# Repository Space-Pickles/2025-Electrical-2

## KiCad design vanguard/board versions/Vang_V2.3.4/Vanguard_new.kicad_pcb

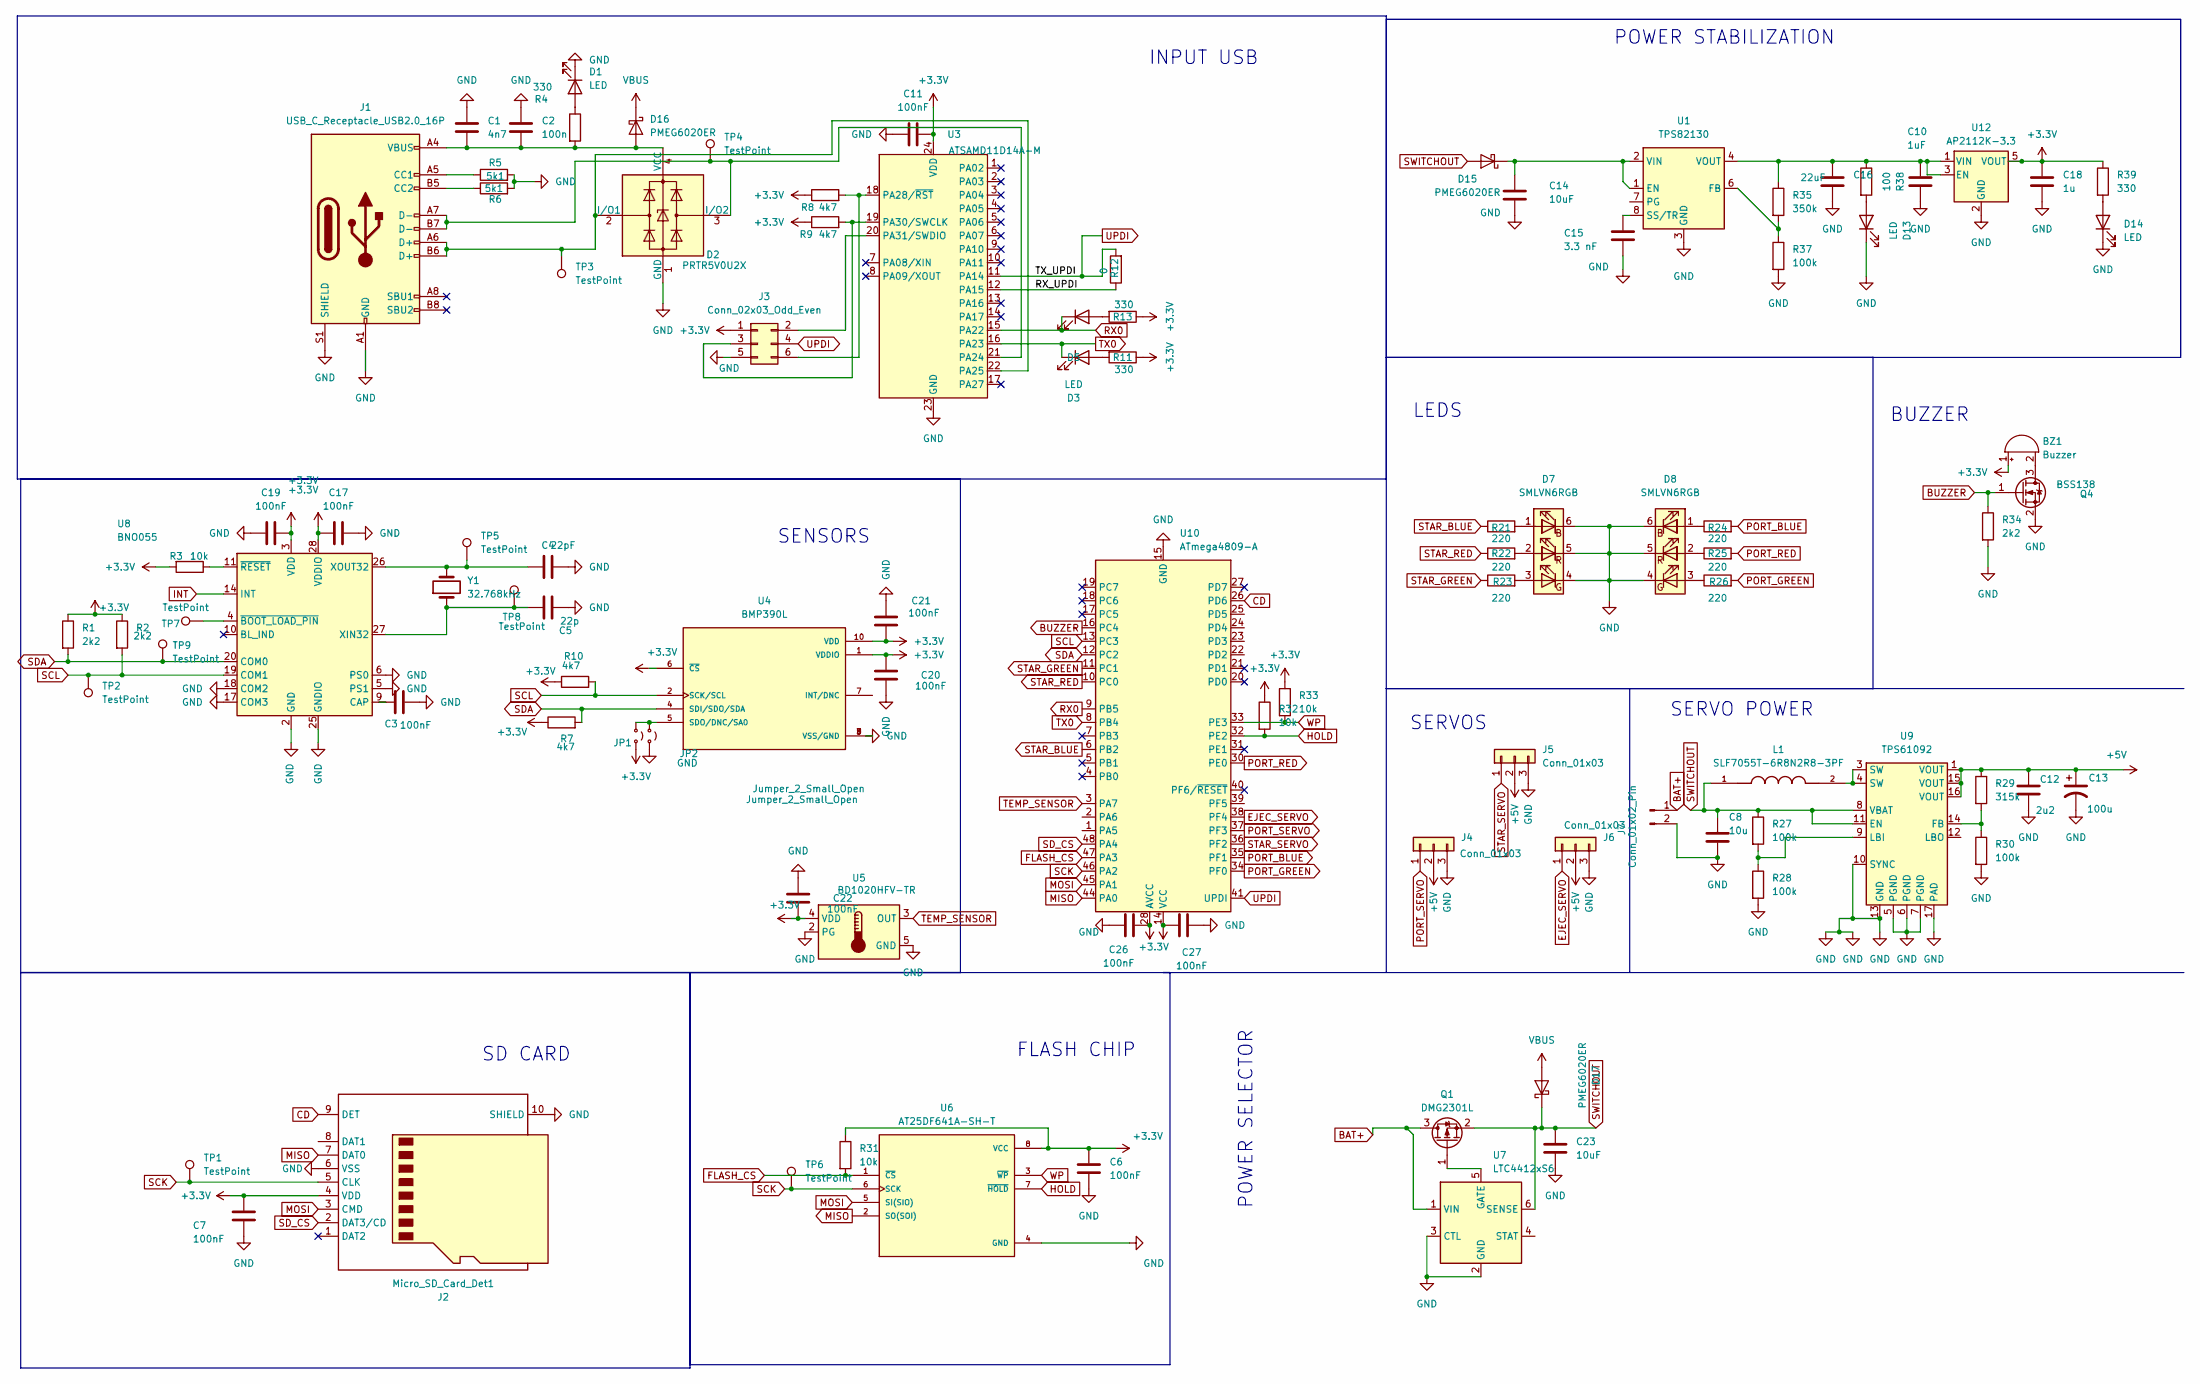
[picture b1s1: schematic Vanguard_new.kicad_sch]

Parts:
BZ1: Buzzer; MagneticBuzzer_PUI_AT-0927-TT-6-R
C1: 4n7; C_0603_1608Metric
C2: 100n; C_0603_1608Metric
C3, C6, C7, C11, C17, C19, C20, C21, C22, C26, C27: 100nF; C_0603_1608Metric
C4: 22pF; C_0603_1608Metric
C5: 22p; C_0603_1608Metric
C8: 10u; C_0603_1608Metric
C10: 1uF; C_0603_1608Metric
C12: 2u2; C_0603_1608Metric
C13: 100u; CP_Radial_D4.0mm_P2.00mm
C14, C23: 10uF; C_0603_1608Metric
C15: 3.3 nF; C_0603_1608Metric
C16: 22uF; C_0603_1608Metric
C18: 1u; C_0603_1608Metric
D1, D3, D5, D13, D14: LED; LED_0603_1608Metric
D2: PRTR5V0U2X; SOT-143
D7, D8: SMLVN6RGB; LED_ROHM_SMLVN6
D15, D16, D17: PMEG6020ER; Nexperia_CFP3_SOD-123W
J1: USB_C_Receptacle_USB2.0_16P; USB_C_Receptacle_Amphenol_124019772112A
J2: Micro_SD_Card_Det1; microSD_HC_Hirose_DM3D-SF
J3: Conn_02x03_Odd_Even; PinHeader_2x03_P2.54mm_Vertical
J4, J5, J6: Conn_01x03; PinHeader_1x03_P2.54mm_Vertical
J7: Conn_01x02_Pin; JST_PH_B2B-PH-K_1x02_P2.00mm_Vertical
JP1, JP2: Jumper_2_Small_Open; SolderJumper-2_P1.3mm_Open_Pad1.0x1.5mm
L1: SLF7055T-6R8N2R8-3PF; L_7.3x7.3_H4.5; PARTREV N/A
Q1: DMG2301L; SOT-23
Q4: BSS138; SOT-23
R1, R2, R34: 2k2; R_0603_1608Metric
R3, R31, R32, R33: 10k; R_0603_1608Metric
R4, R11, R13, R39: 330; R_0603_1608Metric
R5, R6: 5k1; R_0603_1608Metric
R7, R8, R9, R10: 4k7; R_0603_1608Metric
R12: 0; R_0603_1608Metric
R21, R22, R23, R24, R25, R26: 220; R_0603_1608Metric
R27, R28, R30, R37: 100k; R_0603_1608Metric
R29: 315k; R_0603_1608Metric
R35: 350k; R_0603_1608Metric
R38: 100; R_0603_1608Metric
TP1, TP2, TP3, TP4, TP5, TP6, TP7, TP8, TP9: TestPoint; TestPoint_Pad_1.0x1.0mm
U1: TPS82130; Texas_SIL0008D_MicroSiP-8-1EP_2.8x3mm_P0.65mm_EP1.1x1.9mm_T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
U3: ATSAMD11D14A-M; QFN-24-1EP_4x4mm_P0.5mm_EP2.6x2.6mm
U4: BMP390L; ST_HLGA-10_2x2mm_P0.5mm_LayoutBorder3x2y; PARTREV 1.7
U5: BD1020HFV-TR; HVSOF5
U6: AT25DF641A-SH-T; SOIC-8_3.9x4.9mm_P1.27mm; PARTREV 06-2020
U7: LTC4412xS6; TSOT-23-6
U8: BNO055; LGA-28_5.2x3.8mm_P0.5mm
U9: TPS61092; Texas_RSA_VQFN-16-1EP_4x4mm_P0.65mm_EP2.7x2.7mm_ThermalVias
U10: ATmega4809-A; TQFP-48_7x7mm_P0.5mm
U12: AP2112K-3.3; SOT-23-5
Y1: 32.768kHz; Crystal_C26-LF_D2.1mm_L6.5mm_Vertical

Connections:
+5V: C12.1, C13.1, J4.2, J5.2, J6.2, R29.1, U9.1 (VOUT), U9.15 (VOUT), U9.16 (VOUT)
/RX_UPDI: R12.1, U3.12 (PA15)
BAT+: J7.1, Q1.3 (D), U7.1 (VIN)
BUZZER: Q4.1 (G), R34.1, U10.16 (PC4)
CD: J2.9 (DET), U10.26 (PD6)
EJEC_SERVO: J6.1, U10.38 (PF4)
FLASH_CS: R31.2, U6.1 (~CS), U10.47 (PA3)
HOLD: R32.2, U6.7 (~HOLD), U10.32 (PE2)
INT: U8.14 (INT)
MISO: J2.7 (DAT0), U6.2 (SO(SOI)), U10.44 (PA0)
MOSI: J2.3 (CMD), U6.5 (SI(SIO)), U10.45 (PA1)
unnamed: BZ1.2 (-), Q4.3 (D)
unnamed: D1.2 (A), R4.1
unnamed: D2.2 (I/O1), J1.A6 (D+), J1.B6 (D+), TP3.1, U3.22 (PA25)
unnamed: D2.3 (I/O2), J1.A7 (D-), J1.B7 (D-), TP4.1, U3.21 (PA24)
unnamed: D3.2 (A), R11.2
unnamed: D5.2 (A), R13.2
unnamed: D7.1 (BA), R21.2
unnamed: D7.3 (GA), R23.2
unnamed: D7.2 (RA), R22.2
unnamed: D8.1 (BA), R24.1
unnamed: D8.3 (GA), R26.1
unnamed: D8.2 (RA), R25.1
unnamed: D13.2 (A), R38.2
unnamed: D14.2 (A), R39.2
unnamed: C14.1, D15.1 (K), U1.1 (EN), U1.2 (VIN)
unnamed: C1.2, C2.2, D2.4 (VCC), D16.2 (A), J1.A4 (VBUS), J1.A9 (VBUS), J1.B4 (VBUS), J1.B9 (VBUS), R4.2
unnamed: J1.A5 (CC1), R5.1
unnamed: J1.B5 (CC2), R6.1
unnamed: J3.2, U3.20 (PA31/SWDIO)
unnamed: J3.3, R9.2, U3.19 (PA30/SWCLK)
unnamed: J3.6, R8.2, U3.18 (PA28/~RST)
unnamed: JP1.1 (A), JP2.1 (A), U4.5 (SDO/DNC/SA0)
unnamed: L1.2, U9.3 (SW), U9.4 (SW)
unnamed: Q1.1 (G), U7.5 (GATE)
unnamed: R35.2, R37.1, U1.6 (FB)
unnamed: C15.1, U1.8 (SS/TR)
unnamed: C3.1, U8.9 (CAP)
unnamed: C5.1, TP8.1, U8.27 (XIN32), Y1.1
unnamed: C4.1, TP5.1, U8.26 (XOUT32), Y1.2
unnamed: TP7.1, U8.4 (~BOOT_LOAD_PIN)
unnamed: R3.1, U8.11 (~RESET)
unnamed: R29.2, R30.1, U9.14 (FB)
unnamed: R27.2, R28.1, U9.9 (LBI)
unnamed: C10.1, C16.1, R35.1, R38.1, U1.4 (VOUT), U1.5 (VOUT), U12.1 (VIN), U12.3 (EN)
PORT_BLUE: R24.2, U10.35 (PF1)
PORT_GREEN: R26.2, U10.34 (PF0)
PORT_RED: R25.2, U10.30 (PE0)
PORT_SERVO: J4.1, U10.37 (PF3)
RX0: D5.1 (K), U3.15 (PA22), U10.9 (PB5)
SCK: J2.5 (CLK), TP1.1, TP6.1, U6.6 (SCK), U10.46 (PA2)
SCL: R2.2, R10.2, TP2.1, U4.2 (SCK/SCL), U8.19 (COM1), U10.13 (PC3)
SDA: R1.2, R7.2, TP9.1, U4.4 (SDI/SDO/SDA), U8.20 (COM0), U10.12 (PC2)
SD_CS: J2.2 (DAT3/CD), U10.48 (PA4)
STAR_BLUE: R21.1, U10.6 (PB2)
STAR_GREEN: R23.1, U10.11 (PC1)
STAR_RED: R22.1, U10.10 (PC0)
STAR_SERVO: J5.1, U10.36 (PF2)
SWITCHOUT: C8.1, C23.1, D15.2 (A), D17.1 (K), L1.1, Q1.2 (S), R27.1, U7.6 (SENSE), U9.8 (VBAT), U9.11 (EN)
TEMP_SENSOR: U5.3 (OUT), U10.3 (PA7)
TX0: D3.1 (K), U3.16 (PA23), U10.8 (PB4)
UPDI: J3.4, R12.2, U3.11 (PA14), U10.41 (UPDI)
VBUS: D16.1 (K), D17.2 (A)
WP: R33.2, U6.3 (~WP), U10.33 (PE3)

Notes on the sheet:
BUZZER
SENSORS
POWER SELECTOR
SD CARD
INPUT USB
SERVOS
FLASH CHIP
LEDS
POWER STABILIZATION
SERVO POWER

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
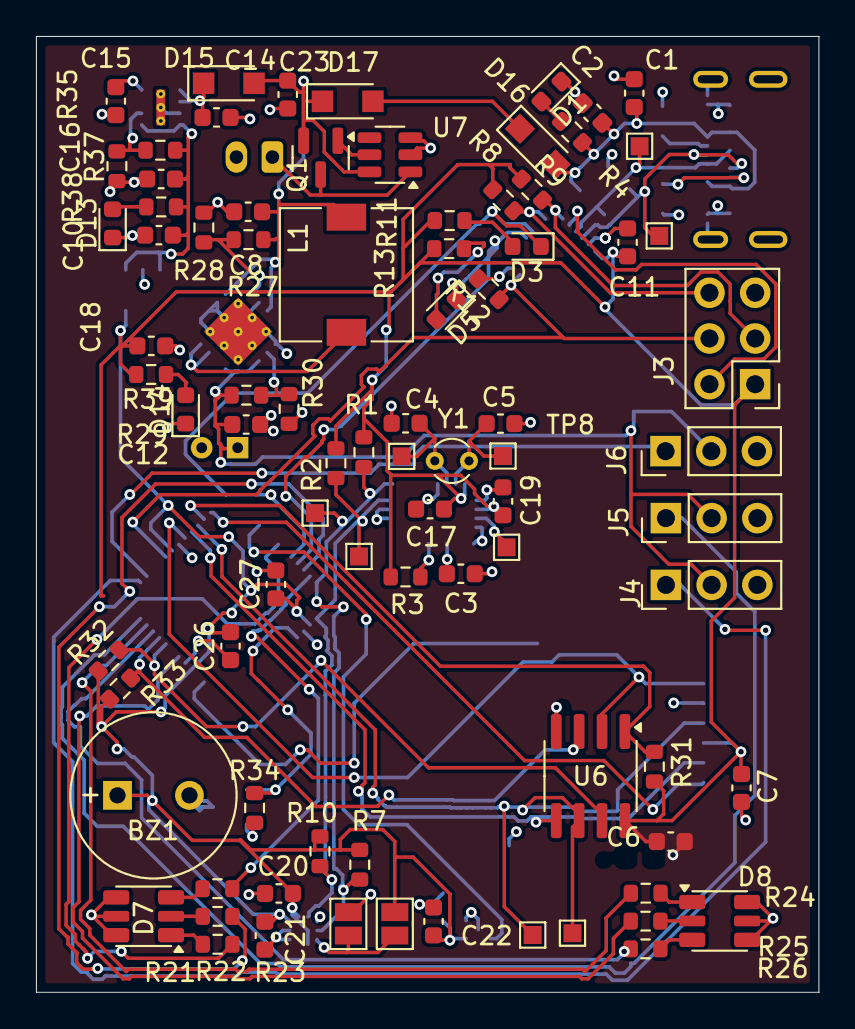
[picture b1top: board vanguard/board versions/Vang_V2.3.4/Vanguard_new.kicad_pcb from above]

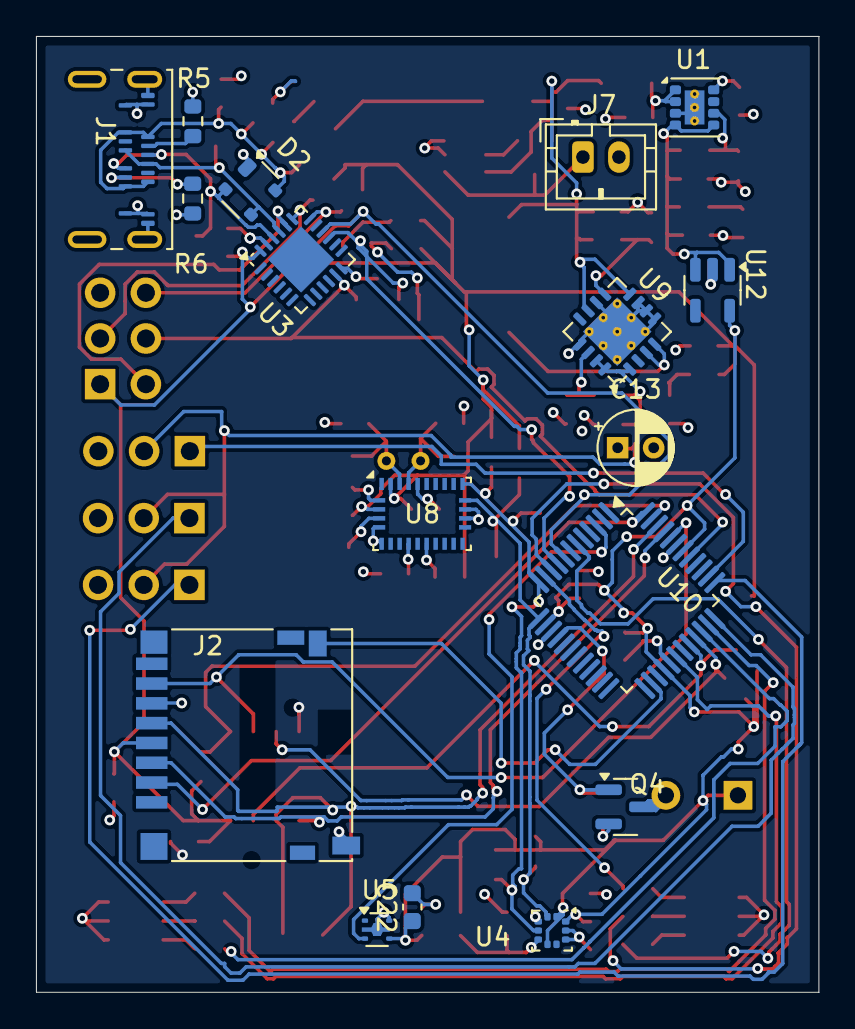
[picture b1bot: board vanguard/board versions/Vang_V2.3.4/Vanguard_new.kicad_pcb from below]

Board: 4 copper layers, 43.5 x 53.1 mm, 100 parts (17 on the bottom side), 65 nets.

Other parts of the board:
C22#2: 100nF; C_0603_1608Metric

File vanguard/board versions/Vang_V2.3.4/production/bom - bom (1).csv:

Designator,Footprint,Quantity,Value,LCSC Part #,,,,
BZ1,MagneticBuzzer_PUI_AT-0927-TT-6-R,1,Buzzer,668-1462-ND,,,,
C1,603,1,4n7,311-1083-1-ND,,,,
C10,603,1,1uF,1276-1946-1-ND,,,,
"C11, C17, C19, C20, C21, C22, C3, C6, C7",603,9,100nF,311-1088-1-ND,,,,
C12,603,1,2u2,1276-1040-1-ND,,,,
C13,CP_Radial_D4.0mm_P2.00mm,1,100u,https://www.adafruit.com/product/2193?gQT=1,,,,
"C14, C23",603,2,10uF,1276-1038-1-ND,,,,
C15,603,1,3.3 nF,478-KGM15AR71E332KTCT-ND,,,,
C16,603,1,22uF,1276-1274-1-ND,,,,
C18,603,1,1u,1276-1946-1-ND,,,,
C2,603,1,100n,311-1088-1-ND,,,,
,,,,,,,,
"C26, C27",201,2,100nF,311-1088-1-ND,,,,
C4,603,1,22pF,478-KGM15ACG1C220KTCT-ND,,,,
C5,603,1,22p,478-KGM15ACG1C220KTCT-ND,,,,
C8,603,1,10u,1276-1038-1-ND,,,,
"D1, D13, D14, D3, D5",201,5,LED,1497-1380-1-ND,,,,
"D15, D16, D17",Nexperia_CFP3_SOD-123W,3,PMEG6020ER,1727-5217-1-ND,,,,
D2,SOT-143,1,PRTR5V0U2X,1727-3884-1-ND,,,,a
"D7, D8",LED_ROHM_SMLVN6,2,SMLVN6RGB,846-1187-1-ND,,,,
J1,USB_C_Receptacle_Amphenol_124019772112A,1,USB_C_Receptacle_USB2.0_16P,664-124019772112ACT-ND,,,,
J2,microSD_HC_Hirose_DM3D-SF,1,Micro_SD_Card_Det1,HR1941CT-ND,,,,
J3,PinHeader_2x03_P2.54mm_Vertical,1,Conn_02x03_Odd_Even,952-2121-ND,,,,
"J4, J5, J6",PinHeader_1x03_P2.54mm_Vertical,3,Conn_01x03,609-3470-ND,,,,
J7,JST_PH_B2B-PH-K_1x02_P2.00mm_Vertical,1,Conn_01x02_Pin,S9014E-02-ND,,,,
"JP1, JP2",SolderJumper-2_P1.3mm_Open_Pad1.0x1.5mm,2,Jumper_2_Small_Open,,,,,
L1,L_7.3x7.3_H4.5,1,SLF7055T-6R8N2R8-3PF,445-4564-1-ND,,,,
Q1,SOT-23,1,DMG2301L,DMG2301L-7DICT-ND,,,,
Q4,SOT-23,1,BSS138,5399-BSS138CT-ND,,,,
"R1, R2, R34",603,3,2k2,311-2.20KHRCT-ND,,,,
"R10, R7, R8, R9",603,4,4k7,311-4.70KHRCT-ND,,,,
"R11, R13, R39, R4",603,4,330,P330DBCT-ND,,,,
R12,603,1,0,311-0.0GRCT-ND,,,,
"R21, R22, R23, R24, R25, R26",603,6,220,A130087CT-ND,,,,
"R27, R28, R30, R37",603,4,100k,311-100KHRCT-ND,,,,
R29,603,1,315k,RMCF0603FT316KCT-ND,,,,
"R3, R31, R32, R33",603,4,10k,2019-RK73H1JTTD1002FCT-ND,,,,
R35,603,1,350k,311-348KHRCT-ND,,,,
R38,603,1,100,P100HCT-ND,,,,
"R5, R6",603,2,5k1,P5.1KBECT-ND,,,,
"TP1, TP2, TP3, TP4, TP5, TP6, TP7, TP8, TP9",TestPoint_Pad_1.0x1.0mm,9,TestPoint,,,,,
U1,Texas_SIL0008D_MicroSiP-8-1EP_2.8x3mm_P0.65mm_EP1.1x1.9mm_ThermalVias,1,TPS82130,296-47436-1-ND,,,,
U10,TQFP-48_7x7mm_P0.5mm,1,ATmega4809-A,150-ATMEGA4809-AU-ND,,,,
U12,SOT-23-5,1,AP2112K-3.3,AP2112K-3.3TRG1DICT-ND,,,,
U3,QFN-24-1EP_4x4mm_P0.5mm_EP2.6x2.6mm,1,ATSAMD11D14A-M,ATSAMD11D14A-MUTCT-ND,,,,
U4,ST_HLGA-10_2x2mm_P0.5mm_LayoutBorder3x2y,1,BMP390L,https://www.mouser.com/ProductDetail/Bosch-Sensortec/BMP390?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,,,,
U5,HVSOF5,1,BD1020HFV-TR,BD1020HFVCT-ND,,,,
U6,SOIC-8_3.9x4.9mm_P1.27mm,1,AT25DF641A-SH-T,1695-AT25DF641A-SH-B-ND,,,,
U7,TSOT-23-6,1,LTC4412xS6,505-LTC4412ES6#TRMPBFCT-ND,,,,
U8,LGA-28_5.2x3.8mm_P0.5mm,1,BNO055,https://www.mouser.com/ProductDetail/Bosch-Sensortec/BNO055?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,,,,
U9,Texas_RSA_VQFN-16-1EP_4x4mm_P0.65mm_EP2.7x2.7mm_ThermalVias,1,TPS61092,296-15240-1-ND,,,,
Y1,Crystal_C26-LF_D2.1mm_L6.5mm_Vertical,1,32.768kHz,300-8301-ND,,,,

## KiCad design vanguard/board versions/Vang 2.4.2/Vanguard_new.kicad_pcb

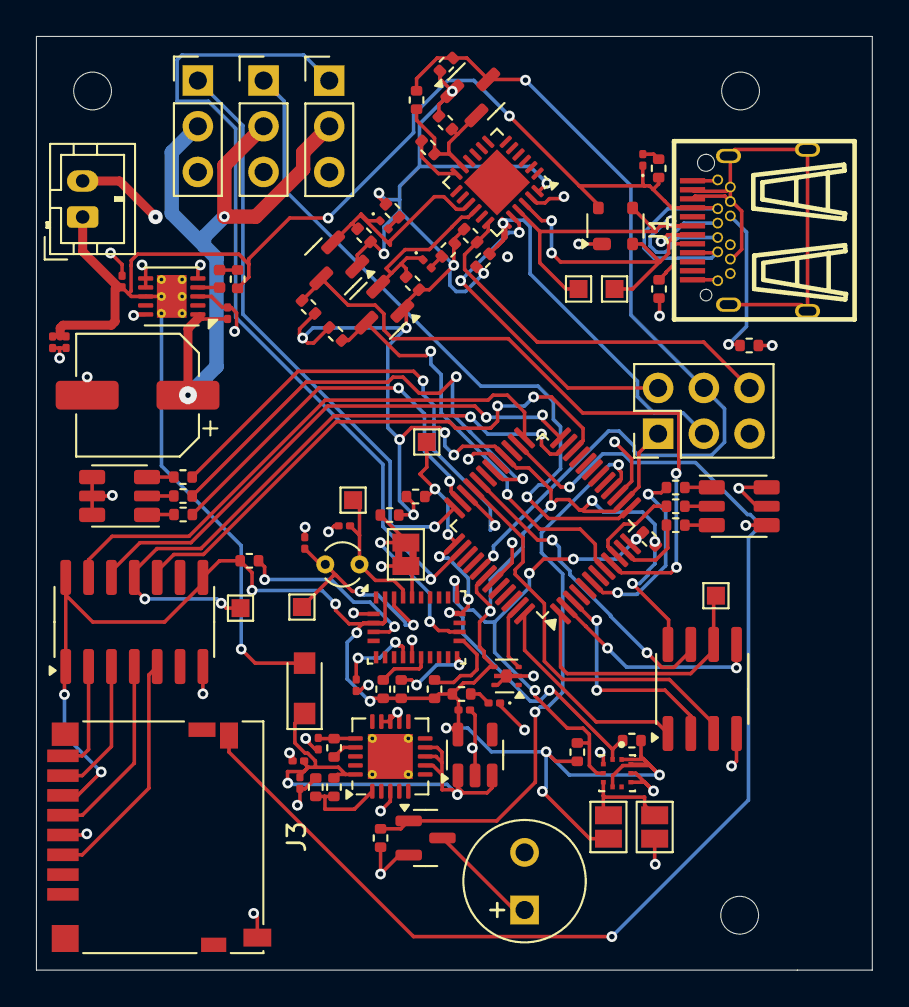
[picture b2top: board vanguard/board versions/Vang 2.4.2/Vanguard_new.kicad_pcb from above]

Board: 4 copper layers, 46.4 x 51.9 mm, 90 parts (0 on the bottom side), 72 nets.

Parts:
ADR1: SolderJumper-2_P1.3mm_Bridged2Bar_Pad1.0x1.5mm
BZ1: Buzzer; MagneticBuzzer_Kingstate_KCG0601
C2, C3: 22p; C_0201_0603Metric
C4, C5: 22u; C_0201_0603Metric
C6, C11: 1u; C_0201_0603Metric
C7: 0u1; C_0201_0603Metric
C8: 10u; C_0201_0603Metric
C9: 2u2; C_0201_0603Metric
C10: 100u; CP_Elec_6.3x5.4
C12: 4n7; C_0201_0603Metric
C13: 100n; C_0201_0603Metric
D1: PRTR5V0U2X; SOT-143
D2, D3, D7: LED; LED_0201_0603Metric
D5: GREEN; LED_0201_0603Metric
D6: PMEG6020ER; Nexperia_CFP3_SOD-123W
J1: USB_C_Receptacle_USB2.0_16P; USB-C-SMD_JLC REPLACEMENT
J2: Conn_02x03_Pin; PinHeader_2x03_P2.54mm_Vertical
J3: Micro_SD_Card_Det1; microSD_HC_Hirose_DM3D-SF
J4: STARBOARD_SERVO; PinHeader_1x03_P2.54mm_Vertical
J5: PORTSIDE_SERVO; PinHeader_1x03_P2.54mm_Vertical
J6: Battery In; JST_PH_B2B-PH-K_1x02_P2.00mm_Vertical
J7: EJECTION_SERVO; PinHeader_1x03_P2.54mm_Vertical
JP1, JP2: Jumper_2_Small_Open; SolderJumper-2_P1.3mm_Open_Pad1.0x1.5mm
L1: 6u8; L_0402_1005Metric
PORTSIDE_RGB1: SMLVN6RGB; LED_ROHM_SMLVN6
Q1, Q2, Q3, Q4: BSS138; SOT-23
R1, R36: 4.7kΩ; R_0402_1005Metric
R2, R6, R7, R9, R10, R11, R12, R13, R19, R20: 4k7; R_0402_1005Metric
R3, R4: 330; R_0402_1005Metric
R5: 0; R_0402_1005Metric
R8: DNP; R_0402_1005Metric
R14, R15: 100k; R_0402_1005Metric
R16: 19k1; R_0402_1005Metric
R17: 330R; R_0402_1005Metric
R18, R23, R24: 10k; R_0402_1005Metric
R21, R22, R34: 2k2; R_0402_1005Metric
R25, R26, R27, R28, R29, R30: 220; R_0402_1005Metric
R31, R32: 5k1; R_0402_1005Metric
R33: 5m; R_0402_1005Metric
R35: R220; R_0402_1005Metric
STARBOARD_RGB1: SMLVN6RGB; LED_ROHM_SMLVN6
TP1, TP2, TP3, TP4, TP5, TP6, TP7: TestPoint; TestPoint_Pad_1.0x1.0mm
U1: ATSAMD11D14A-M; QFN-24-1EP_4x4mm_P0.5mm_EP2.6x2.6mm
U2: ATmega4809-A; TQFP-48_7x7mm_P0.5mm
U3: AT25DF641A-SH-T; SOIC-8_3.9x4.9mm_P1.27mm
U4: AP2112K-3.3; SOT-23-5
U5: BD1020HFV; HVSOF5
U6: BNO086; LGA-28_5.2x3.8mm_P0.5mm
U7: TXB0104D; SOIC-14_3.9x8.7mm_P1.27mm
U8: TPS61092; DFN-10-1EP_3x3mm_P0.5mm_EP1.65x2.38mm_ThermalVias
U9: MPM3610AGQV-P; QFN-20-1EP_4x4mm_P0.5mm_EP2.5x2.5mm_ThermalVias
U10: BMP390L; XDCR_BMP390L
Y1: 32.768kHz; Crystal_C26-LF_D2.1mm_L6.5mm_Vertical

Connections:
+3.3V: C6.1, J2.1, J3.6 (VSS), JP2.2 (B), Q1.1 (G), Q2.1 (G), Q3.1 (G), R1.1, R2.1, R3.1, R4.1, R6.1, R7.1, R9.1, R10.1, R11.1, R12.1, R13.1, R17.1, R18.2, R19.2, R20.2, R21.1, R22.1, R23.1, R24.1, R36.1, U1.24 (VDD), U2.14 (VCC), U2.28 (AVCC), U2.42 (VCC), U3.8 (VCC), U4.5 (VOUT), U5.4 (VDD), U6.3 (VDD), U6.28 (VDDIO), U7.1 (VCCA), U7.8 (OE), U7.14 (VCCB), U10.1 (VDDIO), U10.6 (~CS), U10.10 (VDD)
+5V: C9.1, C10.1, J4.2, J5.2, J7.2, U8.1 (VOUT)
/RX_UPDI: R5.1, U1.12 (PA15)
/TX_UPDI: Q1.2 (S), R5.2, R6.2, R8.1, U1.11 (PA14)
BATT_IN: C8.1, C12.1, C13.1, D1.4 (VCC), D6.2 (A), D7.1 (K), J1.A4 (VBUS), J1.A9 (VBUS), J1.B4 (VBUS), J1.B9 (VBUS), J6.1, R33.2, R35.2, U8.8 (VBAT), U8.11 (EN)
BUZZER: Q4.1 (G), R34.1, U2.16 (PC4)
CD: J3.9 (DET), U2.26 (PD6)
D4: TP3.1, U2.23 (PD3), U7.11 (B3)
D5: U2.22 (PD2), U7.10 (B4)
D6: U2.24 (PD4), U7.12 (B2)
D7: U2.25 (PD5), U7.13 (B1)
EJEC_SERVO: J7.1, U2.38 (PF4)
GND: ADR1.1 (A), BZ1.2 (-), C2.2, C3.2, C4.2, C5.2, C6.2, C7.2, C8.2, C9.2, C10.2, C11.2, C12.2, C13.2, D1.1 (GND), D5.1 (K), J1.A1 (GND), J1.A12 (GND), J1.B1 (GND), J1.B12 (GND), J2.5, J3.4 (VDD), J3.10 (SHIELD), J4.3, J5.3, J6.2, J7.3, JP1.2 (B), PORTSIDE_RGB1.4 (GK), PORTSIDE_RGB1.5 (RK), PORTSIDE_RGB1.6 (BK), Q4.2 (S), R16.2, R31.2, R32.2, R34.2, STARBOARD_RGB1.4 (GK), STARBOARD_RGB1.5 (RK), STARBOARD_RGB1.6 (BK), U1.23 (GND), U2.15 (GND), U2.29 (GND), U2.43 (GND), U3.4 (GND), U4.2 (GND), U5.2 (PG), U5.5 (GND), U6.2 (GND), U6.10 (CLKSEL0), U6.25 (GNDIO), U7.7 (GND), U8.3 (SW), U8.5 (PGND), U8.6 (PGND), U8.7 (PGND), U8.10 (SYNC), U9.3 (AGND), U9.12 (PGND), U9.13 (PGND), U9.14 (PGND), U10.3 (VSS/GND), U10.8 (VSS/GND), U10.9 (VSS/GND)
HOLD: U2.32 (PE2), U3.7 (~HOLD)
unnamed: ADR1.2 (B), R23.2, U6.17 (SA0/H_MOSI)
unnamed: BZ1.1 (+), Q4.3 (D)
unnamed: D1.2 (I/O1), J1.A6 (D+), J1.B6 (D+), TP1.1, U1.22 (PA25)
unnamed: D1.3 (I/O2), J1.A7 (D-), J1.B7 (D-), TP2.1, U1.21 (PA24)
unnamed: D2.2 (A), R4.2
unnamed: D2.1 (K), Q3.2 (S), R9.2, U1.15 (PA22)
unnamed: D3.2 (A), R3.2
unnamed: D3.1 (K), Q2.2 (S), R10.2, U1.16 (PA23)
unnamed: D5.2 (A), R17.2
unnamed: C5.1, C11.1, D6.1 (K), R15.1, U4.1 (VIN), U4.3 (EN), U9.7 (OUT), U9.8 (OUT), U9.9 (OUT), U9.20 (OUT)
unnamed: D7.2 (A), R35.1
unnamed: J1.A5 (CC1), R31.1
unnamed: J1.B5 (CC2), R32.1
unnamed: J2.2, U1.20 (PA31/SWDIO)
unnamed: J2.3, R2.2, U1.19 (PA30/SWCLK)
unnamed: J2.6, R11.2, U1.18 (PA28/~RST)
unnamed: J3.5 (CLK), U7.4 (A3)
unnamed: J3.3 (CMD), U7.5 (A4)
unnamed: J3.7 (DAT0), U7.3 (A2)
unnamed: J3.8 (DAT1), U7.2 (A1)
unnamed: JP1.1 (A), JP2.1 (A), U10.5 (SDO/DNC/SA0)
unnamed: L1.1, R33.1
unnamed: L1.2, U8.4 (SW)
unnamed: PORTSIDE_RGB1.1 (BA), R28.1
unnamed: PORTSIDE_RGB1.3 (GA), R30.1
unnamed: PORTSIDE_RGB1.2 (RA), R29.1
unnamed: R25.2, STARBOARD_RGB1.1 (BA)
unnamed: R27.2, STARBOARD_RGB1.3 (GA)
unnamed: R26.2, STARBOARD_RGB1.2 (RA)
unnamed: C7.1, U6.9 (CAP)
unnamed: R19.1, U6.15 (ENV_SCL)
unnamed: R20.1, U6.16 (ENV_SDA)
unnamed: C3.1, TP5.1, U6.27 (XIN32), Y1.2
unnamed: C2.1, TP6.1, U6.26 (XOUT32/CLKSEL1), Y1.1
unnamed: R24.2, U6.4 (~BOOT)
unnamed: R18.1, U6.11 (~RST)
unnamed: R14.2, U9.17 (EN)
unnamed: R15.2, R16.1, U9.1 (FB)
unnamed: C4.1, R14.1, U9.16 (IN)
PA0/MISO: U2.3 (PA7), U3.2 (SO(SOI))
PA1/MOSI: U2.2 (PA6), U3.5 (SI(SIO))
PA2/SCK: TP4.1, U2.1 (PA5), U3.6 (SCK)
PA3/SS: U2.48 (PA4), U3.1 (~CS)
PORT_BLUE: R28.2, U2.35 (PF1)
PORT_GREEN: R30.2, U2.34 (PF0)
PORT_RED: R29.2, U2.30 (PE0)
PORT_SERVO: J5.1, U2.13 (PC3)
RX0: Q3.3 (D), R12.2, U2.9 (PB5)
SCL: R1.2, R22.2, TP7.1, U2.37 (PF3), U6.19 (H_SCL/SCK/RX), U10.2 (SCK/SCL)
SDA: R21.2, R36.2, U2.12 (PC2), U6.20 (H_SDA/H_MISO/TX), U10.4 (SDI/SDO/SDA)
STAR_BLUE: R25.1, U2.6 (PB2)
STAR_GREEN: R27.1, U2.11 (PC1)
STAR_RED: R26.1, U2.10 (PC0)
STAR_SERVO: J4.1, U2.36 (PF2)
TEMP_SENSOR: U2.47 (PA3), U5.3 (OUT)
TX0: Q2.3 (D), R13.2, U2.8 (PB4)
UPDI: J2.4, Q1.3 (D), R7.2, R8.2, U2.41 (UPDI)
WP: U2.33 (PE3), U3.3 (~WP)

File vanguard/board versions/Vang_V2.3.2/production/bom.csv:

Designator,Footprint,Quantity,Value,LCSC Part #
BZ1,MagneticBuzzer_Kingstate_KCG0601,1,Buzzer,
C10,CP_Elec_6.3x5.4,1,100u,
"C11, C6",0201,2,1u,
C12,0201,1,4n7,
C13,0201,1,100n,
"C2, C3",0201,2,22p,
"C4, C5",0201,2,22u,
C7,0201,1,0u1,
C8,0201,1,10u,
C9,0201,1,2u2,
D1,SOT-143,1,PRTR5V0U2X,
"D2, D3, D7",0201,3,LED,
D5,0201,1,GREEN,
D6,Nexperia_CFP3_SOD-123W,1,PMEG6020ER,
J1,USB_C_Receptacle_GCT_USB4085,1,USB_C_Receptacle_USB2.0_16P,
J2,PinHeader_2x03_P2.54mm_Vertical,1,Conn_02x03_Pin,
J3,microSD_HC_Molex_104031-0811,1,Micro_SD_Card_Det1,
J4,PinHeader_1x03_P2.54mm_Vertical,1,STARBOARD_SERVO,
J5,PinHeader_1x03_P2.54mm_Vertical,1,PORTSIDE_SERVO,
J6,JST_PH_B2B-PH-K_1x02_P2.00mm_Vertical,1,Battery In,
J7,PinHeader_1x03_P2.54mm_Vertical,1,EJECTION_SERVO,
"JP1, JP2",SolderJumper-2_P1.3mm_Open_Pad1.0x1.5mm,2,Jumper_2_Small_Open,
L1,0402,1,6u8,
"PORTSIDE_RGB1, STARBOARD_RGB1",LED_ROHM_SMLVN6,2,SMLVN6RGB,
"Q1, Q2, Q3, Q4",SOT-23,4,BSS138,
"R1, R36",0402,2,4.7kΩ,
"R10, R11, R12, R13, R19, R2, R20, R6, R7, R9",0402,10,4k7,
"R14, R15",0402,2,100k,
R16,0402,1,19k1,
R17,0402,1,330R,
"R18, R23, R24",0402,3,10k,
"R21, R22, R34",0402,3,2k2,
"R25, R26, R27, R28, R29, R30",0402,6,220,
"R3, R4",0402,2,330,
"R31, R32",0402,2,5k1,
R33,0402,1,5m,
R35,0402,1,R220,
R5,0402,1,0,
R8,0402,1,DNP,
"TP1, TP2, TP3, TP4, TP5, TP6, TP7",TestPoint_Pad_1.0x1.0mm,7,TestPoint,
U1,QFN-24-1EP_4x4mm_P0.5mm_EP2.6x2.6mm,1,ATSAMD11D14A-M,
U10,XDCR_BMP390L,1,BMP390L,
U2,TQFP-48_7x7mm_P0.5mm,1,ATmega4809-A,
U3,SOIC-8_3.9x4.9mm_P1.27mm,1,AT25DF641A-SH-T,
U4,SOT-23-5,1,AP2112K-3.3,
U5,HVSOF5,1,BD1020HFV,
U6,LGA-28_5.2x3.8mm_P0.5mm,1,BNO086,
U7,SOIC-14_3.9x8.7mm_P1.27mm,1,TXB0104D,
U8,DFN-10-1EP_3x3mm_P0.5mm_EP1.65x2.38mm_ThermalVias,1,TPS61092,
U9,QFN-20-1EP_4x4mm_P0.5mm_EP2.5x2.5mm_ThermalVias,1,MPM3610AGQV-P,
Y1,Crystal_C26-LF_D2.1mm_L6.5mm_Vertical,1,32.768kHz,

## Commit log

2025-01-29 all old kicad files v2.3
2025-01-29 clean up files
2025-01-29 Chnaged the led seires to parallel
2025-01-29 KiCAD closed
2025-01-29 moved a label and closed Kicad
2025-01-29 removed usbc shield hybrid ground + small changes
2025-01-31 fiverr corrections
2025-01-31 wiring, fiverr, etc
2025-01-31 Ngl i forgot what I did.
2025-02-01 added caps and reistor for emi and esd protection
2025-02-01 removed a reductant vbus connection
2025-02-01 missed gnd wiring
2025-02-01 ran drc
2025-02-01 closed kicad
2025-02-03 kicad opened
2025-02-03 ran drc and assign footprints
2025-02-03 ran sch parity test and assigned a footprint for U9
2025-02-03 @Zumar-shariff
2025-02-03 kicad open
2025-02-03 parity test
2025-02-03 Force revert commit 97deb62d1ea49336f955e200c1b09f92d203a31d
2025-02-03 wired u9 + new drc rules
2025-02-04 fix wiring fixed meddyfix wiring fixed meddyfix wiring fixed meddyfix wiring fixed meddyfix wiring fixed meddyfix wiring fixed meddyfix wiring fixed meddyfix wiring fixed meddyfix wiring fixed meddyf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
2025-02-04 i forgot what i did
2025-02-04 new footprint bmp
2025-02-04 footprint
2025-02-05 bmp370l
2025-02-05 i2c adress changes
2025-02-05 wired mpl370l
2025-02-05 v2.3.2 starting(do not touch)
2025-02-06 added bom text file
2025-02-06 pcb; patrick pls check
2025-02-08 moved crystal + shortened traces
2025-02-10 jst ph battery connector inserted- closeout ready for 5ver review
2025-02-13 changed the BOM
    This reverts commit 83a17ff5912717486ecf69fb1dc7ab8473ef6f21.
2025-02-27 production folder
2025-02-27 cleaned production folder
2025-02-28 PRODUCTION + BOMB
2025-02-28 BOMB BOMB BOMB
2025-03-04 schematic upload
2025-03-06 new folder for usbc
2025-03-06 changed footprint
2025-03-07 imported footprint
2025-03-07 updated parts
2025-03-07 prod files
2025-03-11 + protoboard directory
2025-03-13 bomberdonut
2025-03-14 2.4.2 creation
2025-03-14 not working
2025-03-14 Added BNO055
2025-03-14 BNO055 connections done!!
2025-03-14 checked BNO055 footprints
2025-03-14 Added a buzzer and a voltage regulator, imported symbols
2025-03-15 Opened KICAd
2025-03-15 buck regulator added
2025-03-15 Buck convertor schematic done!
2025-03-15 added an led footprint
2025-03-16 Changed resistor
2025-03-16 Assigned some footprints and annotated
2025-03-16 Added inductor attributes
2025-03-16 footprint config
2025-03-16 footprint config -2
2025-03-17 SMDRI127-6R8NT symbol created and added to the library
2025-03-17 removed new comp and rename BD1020HFV to BD1020HFV-TR
2025-03-17 added new libs
2025-03-17 moved text
2025-03-17 removed a bunch of unused libs
2025-03-17 added CMI-1295-0585T[1]
2025-03-17 added inductor and buck convertor
2025-03-17 BNO055 assigned
2025-03-17 changed buzzer circuit
2025-03-17 changed inductor circuit
2025-03-17 Input USB - r and c assign
2025-03-17 power stabilization
2025-03-17 leds starboard
2025-03-17 sensor - r and c values + a testpoint at boot pin
2025-03-17 servo power r&c
2025-03-17 usb c footpinrt
2025-03-17 its footprint files
2025-03-17 removed inductor files
2025-03-17 inductor footprint thing
2025-03-17 the inductor footprint assigned
    Thank GOD!!! hoho! after 34 hours!
2025-03-17 buzzer footprint assigned!
2025-03-17 assigned barometer footprint
2025-03-21 added button switch
2025-03-31 2.3.2 created, 2.4.1 removed
2025-04-11 opened schematic
2025-04-11 buzzer fix
2025-04-13 fixes
2025-04-14 fixes i forgot
2025-04-14 moved files, cleaned up. imported stuff might need to be re done
2025-04-15 moved 1 file
2025-04-15 updated sch caps
2025-04-16 schematic changes
2025-04-16 renamedfiles
2025-04-21 2.3.3 fix
2025-04-22 made fixes check description
    Removed TXB0104D(image)
    removed the level shifting mosfets
    U11 - changed r35 from 124k to 350, should get the output voltage up
    added shield gnd
    I also reassigned pins on the main mcu
2025-04-24 finished input usb
2025-04-25 started pcb
2025-04-26 dont touch yet
2025-04-26 save spot
2025-04-26 wiring done
2025-04-26 fixed drc, the rest is bs
2025-04-27 added power switch
2025-04-27 2.3.4 ideal diode or and finished pcb layout
2025-04-27 finished everything
2025-04-29 minor changes
2025-05-07 bom + minor fixes
2025-05-11 edits
2025-05-21 production error
